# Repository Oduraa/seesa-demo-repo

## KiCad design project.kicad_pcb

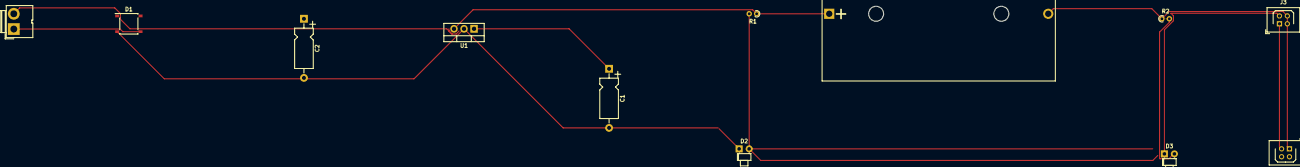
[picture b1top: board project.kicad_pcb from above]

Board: 2 copper layers, 12 parts (0 on the bottom side), 8 nets.

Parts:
C1, C2: CP1; CP_Axial_L10.0mm_D4.5mm_P15.00mm_Horizontal
D1: ABS2; Diode_Bridge_Diotec_ABS
D2, D3: LED; LED_D1.8mm_W1.8mm_H2.4mm_Horizontal_O1.27mm_Z1.6mm
J1: Conn_01x02; JWT_A3963_1x02_P3.96mm_Vertical
J2, J3: Conn_02x02_Odd_Even; Harwin_LTek-Male_2x02_P2.00mm_Vertical
R1, R2: R; R_Axial_DIN0204_L3.6mm_D1.6mm_P1.90mm_Vertical
SW1: SW_DIP_x01; BatteryHolder_Bulgin_BX0036_1xC
U1: LM7805_TO220; TO-220-3_Vertical

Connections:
GND: C1.2, C2.2, D1.2, D2.1, D3.1, J2.3, J2.4, J3.1, J3.2, U1.2
unnamed: C1.1, D1.1, U1.1
unnamed: C2.1, R1.1, SW1.1, U1.3
unnamed: D1.3, J1.1
unnamed: D1.4, J1.2
unnamed: D2.2, R1.2
unnamed: D3.2, R2.2
unnamed: J2.1, J2.2, J3.3, J3.4, R2.1, SW1.2
